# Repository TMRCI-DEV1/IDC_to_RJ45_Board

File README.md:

# IDC_to_RJ45_Board
IDC to female RJ45 converter board for RR-Cirkits BOD-8-SM boards

Shield: [![CC BY-SA 4.0][cc-by-sa-shield]][cc-by-sa]

This work is licensed under a
[Creative Commons Attribution-ShareAlike 4.0 International License][cc-by-sa].

[![CC BY-SA 4.0][cc-by-sa-image]][cc-by-sa]

[cc-by-sa]: http://creativecommons.org/licenses/by-sa/4.0/
[cc-by-sa-image]: https://licensebuttons.net/l/by-sa/4.0/88x31.png
[cc-by-sa-shield]: https://img.shields.io/badge/License-CC%20BY--SA%204.0-lightgrey.svg

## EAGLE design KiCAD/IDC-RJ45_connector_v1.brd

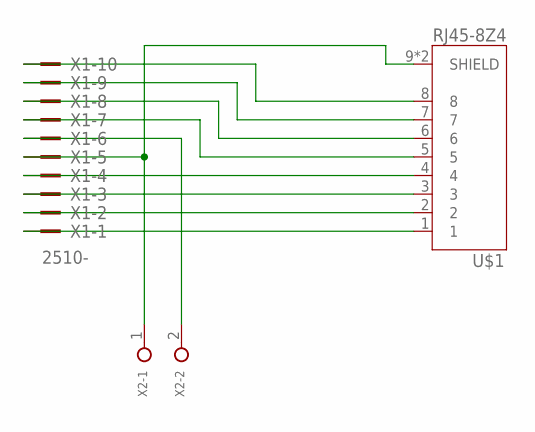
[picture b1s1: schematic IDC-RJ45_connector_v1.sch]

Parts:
U$1: RJ45-8Z4; TE_RJ45-8Z4
X1: 2510-; PAK100/2500-10
X2: TERMINAL-5MM-2POLE; TERMINAL_2P_5MM

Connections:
GND: U$1.9 (SHIELD), U$1.10 (SHIELD), X1.5, X2.1
unnamed: U$1.1, X1.1
unnamed: U$1.2, X1.2
unnamed: U$1.3, X1.3
unnamed: U$1.4, X1.4
unnamed: U$1.5, X1.7
unnamed: U$1.6, X1.8
unnamed: U$1.7, X1.9
unnamed: U$1.8, X1.10
VCC: X1.6, X2.2

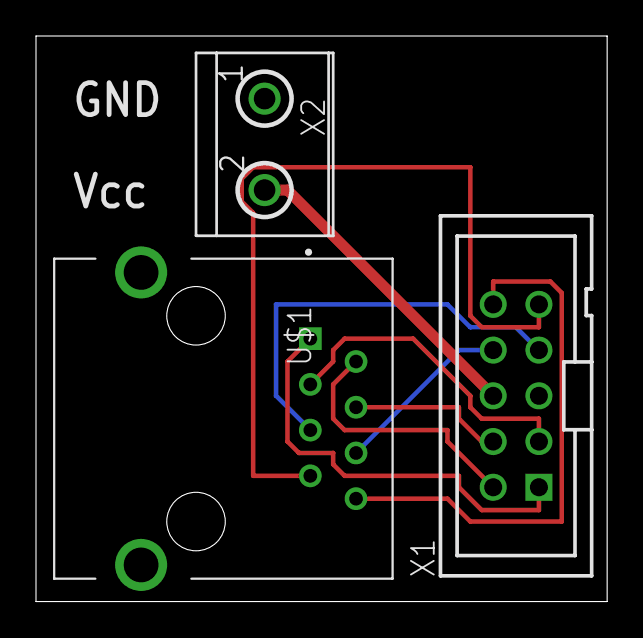
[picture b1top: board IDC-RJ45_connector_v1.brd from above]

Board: 2 copper layers, 31.7 x 31.4 mm, 3 parts (0 on the bottom side), 10 nets.

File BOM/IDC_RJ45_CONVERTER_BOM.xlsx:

Designators | Value | Footprint | Manufacturer Part Number | Quantity
U$1 | CAT 5 MODULAR JACK HIGH | RJ45_CONNECTOR | 5555167-1 | 1 | 5555167-1
X1 | CONN HDR 10POS 0.1 GOLD PCB | IDC_CONNECTOR | SFH11-PBPC-D05-ST-BK | 1 | SFH11-PBPC-D05-ST-BK
X2 | Fixed Terminal Blocks 2 24 Poles, Screw Type, Horizontal, 5.08 Pitch | TERMINAL_2P_5MM | TB007-508-02BE | 1 | 490-TB007-508-02BE

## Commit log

2023-04-12 Added full project
